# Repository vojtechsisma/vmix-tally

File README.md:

# vMix Tally Light (ESP32)

Battery-powered WiFi tally light for [vMix](https://www.vmix.com/). An ESP32 DevKit V1
connects to the vMix TCP API, subscribes to tally updates and drives a red (PROGRAM)
and a green (PREVIEW) LED for one selected input.

## Schematic

Full KiCad project (schematic, PCB, custom symbols and footprints) is in `schematics/`, PDF export in `schematics/vmix_tally_18650.pdf`.

## Hardware

Rev 3, single 18650 cell with a linear 3.3 V regulator.

| Ref    | Part                                                    | Role                                   | Source                                                                                                     |
| ------ | ------------------------------------------------------- | -------------------------------------- | ---------------------------------------------------------------------------------------------------------- |
| U1     | ESP32 DevKit V1 (ESP-WROOM-32, 30 pin, USB-C, CH340)    | MCU, WiFi, web UI                      | [GME 775-652](https://www.gme.cz/v/1519254/vyvojova-deska-esp-wroom-32-usb-c-ch340-esp32)                  |
| BT1    | Panasonic NCR18650GA, 3450 mAh                          | Li-ion cell                            | [GME 540-579](https://www.gme.cz/v/1507018/panasonic-18650ga-li-ion-3450mah-akumulator)                    |
| –      | BHC-18650-1P                                            | Battery holder                         | [GME 819-148](https://www.gme.cz/v/1506919/bhc-18650-1p-drzak-baterie-18650)                               |
| U3     | TP4056 + DW01 module, USB-C                             | Charging, over-discharge protection    | [Drátek](https://dratek.cz/arduino-platforma/34679-nabijeci-deska-li-ion-baterii-usb-c.html) (GME 775-625) |
| U2     | LF33CV (TO-220)                                         | 3.3 V LDO feeding the 3V3 pin directly | [GME 330-165](https://www.gme.cz/v/1488555/stmicroelectronics-lf33cv)                                      |
| –      | CU-TA 020 perfboard, 100 x 50 mm                        | Carrier board                          | GME 661-201                                                                                                |
| –      | CONNFLY BL115G-V8.5, 2x 1x15 pin female header, 2.54 mm | Socket for the ESP32 board             | GME 832-052                                                                                                |
| C1, C2 | 10 µF, 100 µF (optional)                                | LDO output / input capacitors          |                                                                                                            |
| C3, C4 | 100 nF                                                  | Decoupling                             |                                                                                                            |
| D1, D2 | 5 mm LED, red / green                                   | PROGRAM / PREVIEW                      |                                                                                                            |
| R3     | 100 Ω                                                   | Shared LED cathode resistor            |                                                                                                            |
| R1, R2 | 10 kΩ                                                   | 1:2 divider for battery voltage sense  |                                                                                                            |
| SW1    | SPST switch                                             | Power switch                           |                                                                                                            |

Parts list total from GME / Drátek: about 614 Kč (October 2026).

## Firmware

- Connects to vMix on TCP port 8099 and sends `SUBSCRIBE TALLY`.
- Web interface on port 80: status, input selection with names pulled from vMix, brightness, vMix IP, device name, identify (blink LEDs), WiFi credentials. Settings persist in NVS.
- First boot or no WiFi: the device opens its own access point `Tally-XXXX` with a captive portal at `192.168.4.1`. Once home WiFi is configured it is reachable at `http://<name>.local`.
- Battery voltage is averaged and shown in the web UI. The on-board blue LED blinks on low battery.

## Case

3D-printable case in `case/`, OpenSCAD source `tally_box_v3.scad` + STL exports, dimensions can be set in the scad file

To export the scad to stl, set scad path in `case/export_stl.sh` and run it `sh case/export_stl.sh`

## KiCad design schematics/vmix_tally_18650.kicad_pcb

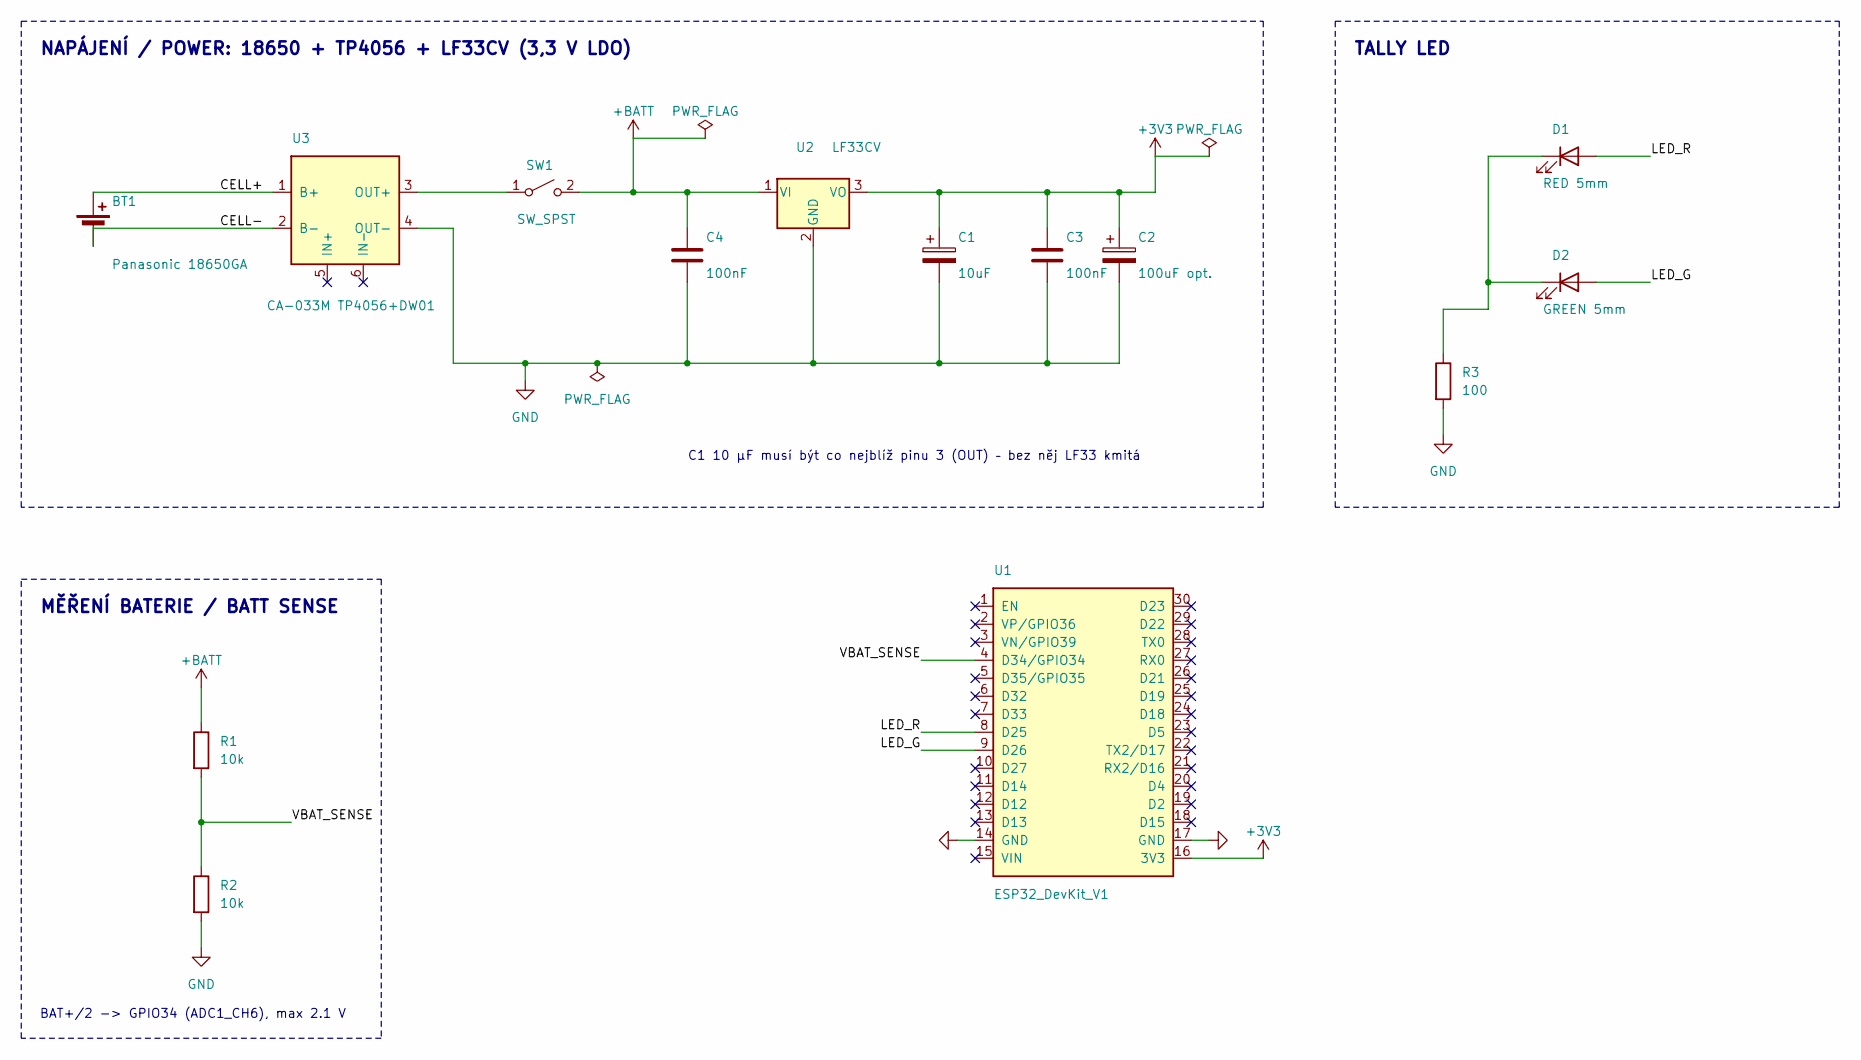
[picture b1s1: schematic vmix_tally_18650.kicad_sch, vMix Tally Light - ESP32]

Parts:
BT1: Panasonic 18650GA; SolderWire-0.5sqmm_1x02_P4.6mm_D0.9mm_OD2.1mm
C1: 10uF; CP_Radial_D5.0mm_P2.00mm
C2: 100uF opt.; CP_Radial_D5.0mm_P2.50mm
C3, C4: 100nF; C_Disc_D5.0mm_W2.5mm_P2.50mm
D1: RED 5mm; LED_D5.0mm
D2: GREEN 5mm; LED_D5.0mm
R1, R2: 10k; R_Axial_DIN0207_L6.3mm_D2.5mm_P10.16mm_Horizontal
R3: 100; R_Axial_DIN0207_L6.3mm_D2.5mm_P10.16mm_Horizontal
SW1: SW_SPST; SolderWire-0.5sqmm_1x02_P4.6mm_D0.9mm_OD2.1mm
U1: ESP32_DevKit_V1; ESP32_DevKit_V1_30pin_Socket
U2: LF33CV; TO-220-3_Vertical
U3: CA-033M TP4056+DW01; TP4056_Module_Wires

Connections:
+3V3: C1.1, C2.1, C3.1, U1.16 (3V3), U2.3 (VO)
+BATT: C4.1, R1.1, SW1.2 (B), U2.1 (VI)
/CELL+: BT1.1 (+), U3.1 (B+)
/CELL-: BT1.2 (-), U3.2 (B-)
/LED_G: D2.2 (A), U1.9 (D26)
/LED_R: D1.2 (A), U1.8 (D25)
/VBAT_SENSE: R1.2, R2.1, U1.4 (D34/GPIO34)
GND: C1.2, C2.2, C3.2, C4.2, R2.2, R3.2, U1.14 (GND), U1.17 (GND), U2.2 (GND), U3.4 (OUT-)
unnamed: D1.1 (K), D2.1 (K), R3.1
unnamed: SW1.1 (A), U3.3 (OUT+)

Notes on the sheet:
C1 10 µF musí být co nejblíž pinu 3 (OUT) – bez něj LF33 kmitá
BAT+/2 -> GPIO34 (ADC1_CH6), max 2.1 V
NAPÁJENÍ / POWER: 18650 + TP4056 + LF33CV (3,3 V LDO)
TALLY LED
MĚŘENÍ BATERIE / BATT SENSE

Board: 2 copper layers, 14 parts (0 on the bottom side), 10 nets, no tracks yet.
